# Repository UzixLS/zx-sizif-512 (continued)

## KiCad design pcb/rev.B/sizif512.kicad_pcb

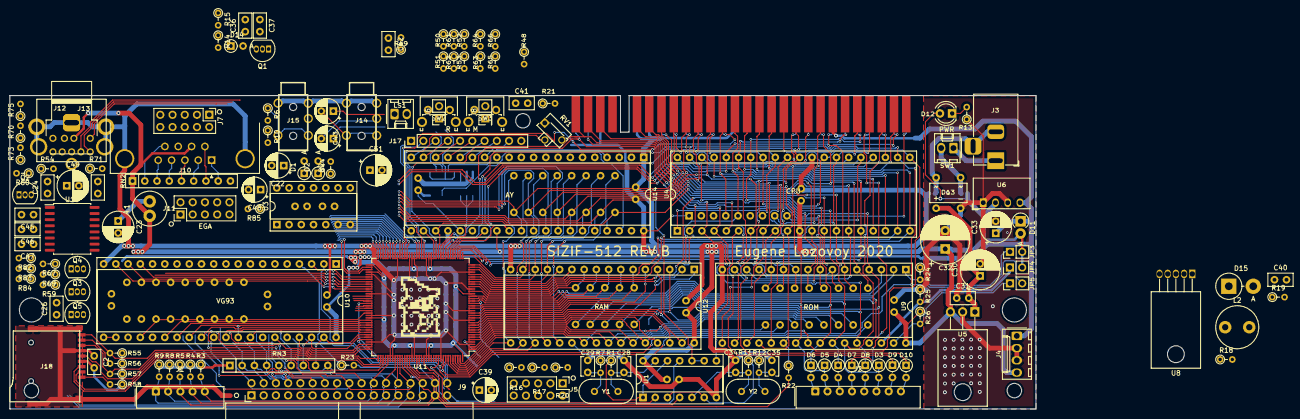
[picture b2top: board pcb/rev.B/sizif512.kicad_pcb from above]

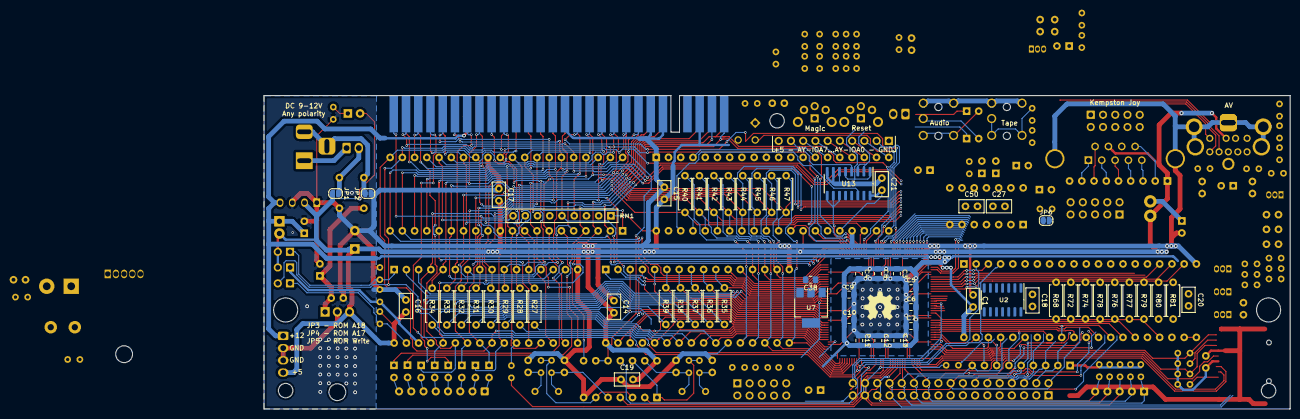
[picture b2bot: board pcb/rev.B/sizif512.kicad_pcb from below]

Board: 2 copper layers, 213.0 x 65.1 mm, 214 parts (61 on the bottom side), 231 nets.

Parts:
C1, C2, C14, C15, C16, C17, C18, C19, C20, C21, C24, C25, C26, C27, C31, C36, C40, C41, C45, C46, C47, C50: 100n; C_Disc_D5.0mm_W2.5mm_P2.50mm
C3, C4, C5, C6, C7, C8, C9, C10, C11, C12, C13, C38: 100n; C_0805_2012Metric_Pad1.15x1.40mm_HandSolder
C22, C43, C44, C48: 10u/16V; CP_Radial_D5.0mm_P2.50mm
C23, C49, C51: 220u/16V; CP_Radial_D6.3mm_P2.50mm
C28, C34: 33p; C_Disc_D3.8mm_W2.6mm_P2.50mm
C29, C35: 47p; C_Disc_D3.8mm_W2.6mm_P2.50mm
C30: 100u/50V; CP_Radial_D8.0mm_P2.50mm
C32: 470u/25V; CP_Radial_D10.0mm_P3.80mm
C33: 100u/25V; CP_Radial_D6.3mm_P2.50mm
C37: 10n; C_Disc_D5.0mm_W2.5mm_P2.50mm
C39: 100u/16V; CP_Radial_D5.0mm_P2.50mm
C42: 47n; C_Disc_D5.0mm_W2.5mm_P2.50mm
D1, D2: 1N4148; D_DO-35_SOD27_P2.54mm_Vertical_AnodeUp
D3, D4, D5, D6, D7, D8, D9, D10, D14: BAT85; D_DO-35_SOD27_P2.54mm_Vertical_AnodeUp
D11: 1N5817; D_DO-41_SOD81_P2.54mm_Vertical_AnodeUp
D12: LED; LED_D4.0mm
D13: DB207; DB-1
D15: D; D_DO-201AD_P5.08mm_Vertical_AnodeUp
H1, H2: MountingHole; MountingHole_5mm
H3, H4, H5: MountingHole; MountingHole_3mm
J1: Conn_01x05; FFC_FPC_1x05
J2: Conn_01x08; FFC_FPC_1x08
J3: DS-210; BarrelJack_Horizontal
J4: WF-4; Molex_KK-254_AE-6410-04A_1x04_P2.54mm_Vertical
J5: JTAG; PinHeader_2x05_P2.54mm_Vertical
J6, J8: Conn_01x02; PinHeader_2x01_P2.54mm_Vertical
J7: Conn_02x05_Top_Bottom; PinHeader_2x05_P2.54mm_Vertical
J9: Conn_02x17_Odd_Even; IDC-Header_2x17_P2.54mm_Horizontal_Mirrored
J10: DB9-M; DSUB-9_Male_Horizontal_P2.77x2.84mm_EdgePinOffset4.94mm_Hou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
J11: Conn_02x05_Odd_Even; PinHeader_2x05_P2.54mm_Vertical
J12: Mini-DIN-9; minidin-9
J13: RCJ-014; CUI_RCJ-01X-WIDE
J14, J15: PJ-313
J16: Conn_02x28_Row_Letter_First; ZX_EDGE
J17: Conn_01x10; PinHeader_1x10_P2.54mm_Vertical
J18: MEM2055-00-190-01-A; GCT-MEM2055-00-190-01-A
JP1, JP2, JP6: SolderJumper_2_Open; SolderJumper-2_P1.3mm_Open_RoundedPad1.0x1.5mm
JP3, JP4, JP5: Jumper; PinHeader_1x02_P2.54mm_Vertical
L1: 220u/0.2A; L_Radial_D7.0mm_P3.00mm
L2: L; L_Radial_D8.7mm_P5.00mm_Fastron_07HCP
LOGO1: Logo_Open_Hardware_Small; OSHW-Symbol_6.7x6mm_SilkScreen
LOGO2: graphic; black-mage2
LS1: WF-2; Molex_KK-254_AE-6410-02A_1x02_P2.54mm_Vertical
Q1: BC547B; TO-92_Inline
Q2, Q3, Q4, Q5: BC547C; TO-92_Inline
R1, R11: 1M; R_Axial_DIN0204_L3.6mm_D1.6mm_P2.54mm_Vertical
R2, R10: 47k; R_Axial_DIN0204_L3.6mm_D1.6mm_P2.54mm_Vertical
R3, R4, R5, R8, R9, R16, R17, R20, R23, R24, R25, R26, R55, R56, R57, R58, R65, R66: 10k; R_Axial_DIN0204_L3.6mm_D1.6mm_P2.54mm_Vertical
R6, R7, R12, R15, R52, R53, R63, R64: 1k; R_Axial_DIN0204_L3.6mm_D1.6mm_P2.54mm_Vertical
R13, R18, R19, R22, R48: 470; R_Axial_DIN0204_L3.6mm_D1.6mm_P2.54mm_Vertical
R14: 220k; R_Axial_DIN0204_L3.6mm_D1.6mm_P2.54mm_Vertical
R21, R85: 100k; R_Axial_DIN0204_L3.6mm_D1.6mm_P2.54mm_Vertical
R27, R28, R29, R30, R31, R32, R33, R34, R35, R36, R37, R38, R39, R40, R41, R42, R43, R44, R45, R46, R47: 1k; R_Axial_DIN0207_L6.3mm_D2.5mm_P7.62mm_Horizontal
R49, R54, R60: 270; R_Axial_DIN0204_L3.6mm_D1.6mm_P2.54mm_Vertical
R50, R51, R61, R62: 2k; R_Axial_DIN0204_L3.6mm_D1.6mm_P2.54mm_Vertical
R59, R67, R69, R70, R73, R75: 68; R_Axial_DIN0204_L3.6mm_D1.6mm_P2.54mm_Vertical
R68, R72, R74, R76, R77, R78, R79, R80, R81: 3.6k; R_Axial_DIN0207_L6.3mm_D2.5mm_P7.62mm_Horizontal
R71, R82, R83, R84: 75; R_Axial_DIN0204_L3.6mm_D1.6mm_P2.54mm_Vertical
RN1, RN2: 10k; R_Array_SIP9
RN3: 4.7k; R_Array_SIP9
RV1: 47k; Potentiometer_Runtron_RM-063_Horizontal
SW1: Conn_01x02; Molex_KK-254_AE-6410-02A_1x02_P2.54mm_Vertical
SW2, SW3: WF-2; SW_Tactile_SPST_Angled_PTS645Vx83-2LFS
U1, U3: 74HCU04; DIP-14_W7.62mm_Socket
U2: 74HCT05; SOIC-14_3.9x8.7mm_P1.27mm
U4: Z84C0008PEC; DIP-40_W15.24mm_Socket
U5: L4940V5 / K7805-2000R3L; TO-220-3_Horizontal_TabDown
U6: AM1S-0512SZ; Converter_DCDC_muRata_CRE1xxxxxx3C_THT
U7: AMS1117-3.3; SOT-223-3_TabPin2
U8: LM2596T-ADJ; TO-220-5_Horizontal_TabDown
U9: 29C040; DIP-32_W15.24mm_Socket
U10: 1818VG93; DIP-40_W15.24mm_Socket
U11: EPM3256ATC144; TQFP-144_20x20mm_P0.5mm
U12: AS6C4008-55PCN; DIP-32_W15.24mm_Socket
U13: 74HCT4053D; SOIC-16_3.9x9.9mm_P1.27mm
U14: AY-3-8310; DIP-40_W15.24mm_Socket
U15: AD724; SOIC-16W_7.5x10.3mm_P1.27mm
Y1: 17.734475 MHz; Crystal_HC49-U_Vertical
Y2: 8 MHz; Crystal_HC49-U_Vertical

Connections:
+3V3: C2.2, C3.2, C4.2, C5.2, C6.2, C7.2, C8.2, C9.2, C10.2, C11.2, C12.2, C13.2, C39.1, J5.4, J18.4, R16.2, R17.2, R55.1, R56.1, R57.1, R58.1, U7.2, U11.24, U11.50, U11.51, U11.58, U11.73, U11.76, U11.95, U11.115, U11.123, U11.130, U11.144
+5V: C14.2, C15.2, C16.2, C17.2, C18.2, C19.2, C20.2, C21.2, C32.1, C38.2, D11.2, D12.2, J4.4, J7.4, J10.7, J12.2, J16.A3, J17.10, JP1.2, JP3.2, JP4.2, JP6.1, L1.1, R3.1, R4.1, R5.1, R8.1, R9.1, R14.1, R21.2, R23.1, R26.1, RN1.1, RN2.1, RN3.1, U1.14, U2.14, U4.11, U5.3, U6.2, U7.3, U9.32, U10.21, U10.22, U12.32, U13.16, U14.25, U14.28, U14.40
+5VA: C23.1, C24.2, C25.2, C26.2, C27.2, L1.2, Q2.1, Q3.1, Q4.1, Q5.1, U3.14, U15.4, U15.5, U15.14, U15.15
+12V: C1.2, C33.1, D11.1, J4.1, J16.B22, U6.4, U10.40
/<: J16.A13, R48.1, U11.54
/>: R48.2, U11.53
/A0: J16.A9, R27.1, U4.30, U9.12
/A1: J16.A10, R28.1, U4.31, U9.11
/A2: J16.A11, R29.1, U4.32, U9.10
/A3: J16.A12, R30.1, U4.33, U9.9
/A4: J16.A24, R31.1, U4.34, U9.8
/A5: J16.A23, R32.1, U4.35, U9.7, U10.5
/A6: J16.A22, R33.1, U4.36, U9.6, U10.6
/A7: J16.A21, R34.1, U4.37, U9.5
/A8: D3.1, J16.B26, R35.1, U4.38, U9.27
/A9: D4.1, J16.A27, R36.1, U4.39, U9.26
/A10: D5.1, J16.B27, R37.1, U4.40, U9.23
/A11: D6.1, J16.A28, R38.1, U4.1, U9.25
/A12: D7.1, J16.A2, R39.1, U4.2, U9.4
/A13: D8.1, J16.B2, U4.3, U9.28, U11.132
/A14: D9.1, J16.A1, U4.4, U11.46
/A15: D10.1, J16.B1, U4.5, U11.48
/AY_ABC: U11.43, U13.9, U13.10, U13.11
/AY_BC1: U11.41, U14.29
/AY_BDIR: U11.42, U14.27
/AY_CLK: U11.49, U14.22
/Blue: J11.1, R74.1, U11.74
/Bright: J11.4, J11.8, J11.9, R76.2, R77.2, R78.2, U11.70
/CLK8: U1.4, U11.125
/CLK17: U1.2, U11.128, U15.3
/CLKCPU: U1.8, U4.6
/CLKCPU0: U1.11, U11.134
/Csync: Q2.2, U11.75, U15.16
/D0: J16.B6, R40.1, U4.14, U9.13, U10.7, U14.37
/D1: J16.B7, R41.1, U4.15, U9.14, U10.8, U14.36
/D2: J16.B8, R42.1, U4.12, U9.15, U10.9, U14.35
/D3: J16.B11, R43.1, U4.8, U9.17, U10.10, U14.34
/D4: J16.B12, R44.1, U4.7, U9.18, U10.11, U14.33
/D5: J16.B10, R45.1, U4.9, U9.19, U10.12, U14.32
/D6: J16.B9, R46.1, U4.10, U9.20, U10.13, U14.31
/D7: J16.B3, R47.1, U4.13, U9.21, U10.14, U14.30
/FD_CLK: U10.24, U11.93
/FD_CS: U10.3, U11.78
/FD_DDEN: U10.37, U11.106
/FD_DIR: U2.3, U10.16
/FD_DISK0: J9.14, U11.92
/FD_DISK1: J9.12, RN3.5, U11.86
/FD_DRQ: RN3.7, U10.38, U11.103
/FD_HLT: U10.23, U11.90
/FD_INDEX: J9.8, RN3.2, U11.91
/FD_INDEX1: U10.35, U11.107
/FD_INTRQ: RN3.8, U10.39, U11.102
/FD_MOTOR: U2.13, U10.28, U10.32, U11.98
/FD_RAWR: U10.27, U11.97
/FD_RDAT: J9.30, RN3.9, U11.84
/FD_RST: U10.19, U11.83
/FD_S: U10.26, U11.96
/FD_SIDE: U2.9, U11.88
/FD_SL: U10.17, U11.81
/FD_SR: U10.18, U11.82
/FD_STEP: U2.1, U10.15
/FD_TR00: J9.26, RN3.3, U10.34
/FD_TR43: U10.29, U11.99
/FD_WD: U10.31, U11.100
/FD_WDAT: U2.5, U11.87
/FD_WF_DE: RN3.6, U10.33, U11.101
/FD_WPT: J9.28, RN3.4, U10.36
/FD_WSTB: U2.11, U10.30
/Green: J11.2, R72.1, U11.71
/Hsync: J11.7, U11.80
/KA8: D3.2, J2.6
/KA9: D4.2, J2.3
/KA10: D5.2, J2.2
/KA11: D6.2, J2.1
/KA12: D7.2, J2.4
/KA13: D8.2, J2.5
/KA14: D9.2, J2.7
/KA15: D10.2, J2.8
/KD0: J1.1, R9.2, U11.116
/KD1: J1.2, R8.2, U11.113
/KD2: J1.3, R5.2, U11.121
/KD3: J1.4, R4.2, U11.120
/KD4: J1.5, R3.2, U11.119
/RA14: U9.29, U11.25
/RA15: U9.3, U11.22
/RA16: U9.2, U11.23
/Red: J11.3, R68.1, U11.72
/SD_CD: J18.9, R55.2, U11.108
/SD_CS: J18.2, U11.111
/SD_MISO: J18.7, R57.2, U11.109
/SD_MOSI: J18.3, U11.112
/SD_SCK: J18.5, U11.110
/SND_DAC: R49.1, U11.61
/SND_L: C43.2, J12.8, J14.T
/SND_MONO: C48.2, J12.6
/SND_R: C44.2, J12.9, J14.R
/TAPE_IN: J15.R, J15.T, R6.1
/TAPE_IN0: RN2.9, U3.12, U11.55
/TCK: J5.1, R20.2, U11.89
/TDI: J5.9, R16.1, U11.4
/TDO: J5.3, U11.104
/TMS: J5.5, R17.1, U11.20
/VA0: R27.2, U11.6, U12.27
/VA1: R28.2, U11.7, U12.28
/VA2: R29.2, U11.5, U12.26
/VA3: R30.2, U11.2, U12.25
/VA4: R31.2, U11.143, U12.23
/VA5: R32.2, U11.12, U12.4
/VA6: R33.2, U11.11, U12.3
/VA7: R34.2, U11.10, U12.31
/VA8: R35.2, U11.27, U12.10
/VA9: R36.2, U11.21, U12.9
/VA10: R37.2, U11.19, U12.8
/VA11: R38.2, U11.18, U12.7
/VA12: R39.2, U11.16, U12.6
/VA13: U11.15, U12.5
/VA14: U11.34, U12.12
/VA15: U11.32, U12.11
/VA16: U11.28, U12.2
/VA17: U11.9, U12.30
/VA18: U11.14, U12.1
/VD0: R40.2, U11.142, U12.21
/VD1: R41.2, U11.35, U12.13
/VD2: R42.2, U11.141, U12.20
/VD3: R43.2, U11.36, U12.14
/VD4: R44.2, U11.138, U12.19
/VD5: R45.2, U11.37, U12.15
/VD6: R46.2, U11.139, U12.18
/VD7: R47.2, U11.140, U12.17
/VID_B: J12.1, R75.2
/VID_COMP: J12.4, J13.1, R71.2
/VID_G: J12.3, R73.2
/VID_R: J12.7, R70.2
/VID_SYNC: J12.5, R54.2
/Vsync: J11.6, U11.79
/~BUSACK: J16.A26, U4.23
/~BUSRQ: J16.A19, RN1.9, U4.25
/~CLKCPU: J16.A8, U1.9, U1.10
/~HALT: J16.B15, U4.18
/~INT: J16.B13, RN1.4, U4.16, U11.38
/~IORQ: J16.B17, U4.20, U11.31
/~JOY_B1: J7.2, J10.6, RN2.7, U11.63
/~JOY_B2: J7.8, J10.9, RN2.2, U11.69
/~JOY_B3: J7.9, J10.5, RN2.3, U11.68
/~JOY_DOWN: J7.3, J10.2, RN2.6, U11.65
/~JOY_LEFT: J7.5, J10.3, RN2.5, U11.66
/~JOY_RIGHT: J7.7, J10.4, RN2.4, U11.67
/~JOY_UP: J7.1, J10.1, RN2.8, U11.62
/~M1: J16.B24, U4.27, U11.40
/~MREQ: J16.B16, U4.19, U11.30
/~NMI: J16.B14, RN1.5, U4.17, U11.39
/~RD: J16.B18, RN1.6, U4.21, U9.24, U10.4, U11.137
/~RFSH: J16.B25, U4.28, U11.29
/~ROMCS: J16.A25, R22.1, U9.22
/~ROMCS0: R22.2, U11.122
/~RSTCPU: J16.A20, RN1.7, U4.26, U11.47, U14.23
/~VRD: U11.1, U12.24
/~VWR: U11.8, U12.29
/~WAIT: J16.B21, RN1.8, U4.24
/~WR: J16.B19, JP5.2, U4.22, U10.2, U11.136
GND: C1.1, C2.1, C3.1, C4.1, C5.1, C6.1, C7.1, C8.1, C9.1, C10.1, C11.1, C12.1, C13.1, C14.1, C15.1, C16.1, C17.1, C18.1, C19.1, C20.1, C21.1, C23.2, C24.1, C25.1, C26.1, C27.1, C28.1, C29.1, C30.2, C31.1, C32.2, C33.2, C34.1, C35.1, C37.1, C38.1, C39.2, C41.1, C42.1, D13.1, D14.2, D15.2, J4.2, J4.3, J5.2, J5.10, J6.2, J7.6, J7.10, J8.2, J9.1, J9.3, J9.5, J9.7, J9.9, J9.11, J9.13, J9.15, J9.17, J9.19, J9.21, J9.23, J9.25, J9.27, J9.29, J9.31, J9.33, J10.0, J10.8, J11.5, J12.0, J13.2, J14.S, J15.S, J16.A6, J16.A7, J16.A14, J17.1, J18.6, J18.10, JP2.2, LS1.2, Q1.3, R10.1, R13.1, R20.1, R24.1, R25.1, R60.2, R63.2, R64.2, R79.2, R80.2, R81.2, R82.2, R83.2, R84.2, RV1.3, SW2.1, SW3.1, U1.7, U2.7, U3.7, U4.29, U5.2, U6.1, U6.3, U7.1, U8.3, U8.5, U9.16, U10.20, U11.3, U11.13, U11.17, U11.26, U11.33, U11.52, U11.57, U11.59, U11.64, U11.77, U11.85, U11.94, U11.105, U11.114, U11.124, U11.129, U11.135, U12.16, U12.22, U13.6, U13.7, U13.8, U14.1, U14.24, U15.1, U15.2, U15.12, U15.13
unnamed: C22.1, D1.2, D2.1, R10.2, U3.9
unnamed: C22.2, R6.2
unnamed: C28.2, R1.2, U1.13, Y1.1
unnamed: C29.2, R7.2, Y1.2
unnamed: C30.1, C31.2, D13.4, U5.1
unnamed: C34.2, R11.2, U1.5, Y2.1
unnamed: C35.2, R12.2, Y2.2
unnamed: C36.1, C37.2, D14.1, Q1.2, R14.2
unnamed: C36.2, R15.2
unnamed: C42.2, R49.2, R50.2, R51.1
unnamed: C43.1, R51.2, R52.1, R62.1, R64.1, R66.1
unnamed: C44.1, R50.1, R53.2, R61.2, R63.1, R65.2
unnamed: C45.1, R59.2
unnamed: C45.2, U15.6
unnamed: C46.1, R67.2
unnamed: C46.2, U15.7
unnamed: C47.1, R69.2
unnamed: C47.2, U15.8
unnamed: C48.1, R65.1, R66.2, RV1.2
unnamed: C49.1, U15.10
unnamed: C49.2, R71.1
unnamed: C50.1, R85.1, U3.1
unnamed: C50.2, RV1.1
unnamed: C51.1, R85.2, U3.6
unnamed: C51.2, LS1.1
unnamed: D1.1, D2.2, R2.1, U3.8, U3.11
unnamed: D12.1, R13.2
unnamed: D13.2, JP1.1, SW1.2
unnamed: D13.3, J3.2, J3.3, JP2.1
unnamed: J3.1, SW1.1
unnamed: J9.10, J9.16, U2.12
unnamed: J9.18, U2.4
unnamed: J9.20, U2.2
unnamed: J9.22, U2.6
unnamed: J9.24, U2.10
unnamed: J9.32, U2.8
unnamed: J11.10, JP6.2
unnamed: J17.2, U14.21
unnamed: J17.3, U14.20
unnamed: J17.4, U14.19
unnamed: J17.5, U14.18
unnamed: J17.6, U14.17
unnamed: J17.7, U14.16
unnamed: J17.8, U14.15
unnamed: J17.9, U14.14
unnamed: J18.1, R58.2
unnamed: J18.8, R56.2
unnamed: JP3.1, R24.2, U9.1
unnamed: JP4.1, R25.2, U9.30
unnamed: JP5.1, R26.2, U9.31
unnamed: Q2.3, R54.1, R60.1
unnamed: Q3.2, R68.2, R78.1, R81.1
unnamed: Q3.3, R59.1, R70.1, R82.1
unnamed: Q4.2, R72.2, R77.1, R80.1
unnamed: Q4.3, R67.1, R73.1, R83.1
unnamed: Q5.2, R74.2, R76.1, R79.1
unnamed: Q5.3, R69.1, R75.1, R84.1
unnamed: R1.1, R7.1, U1.1, U1.12
unnamed: R2.2, U3.10, U3.13
unnamed: R11.1, R12.1, U1.3, U1.6
unnamed: R52.2, U13.12, U13.13
unnamed: R53.1, U13.2, U13.3
unnamed: R61.1, R62.2, U13.1, U13.5
unnamed: U3.2, U3.3
unnamed: U3.4, U3.5
unnamed: U13.4, U14.3
unnamed: U13.14, U14.4
unnamed: U13.15, U14.38
~MAGIC: J8.1, R23.2, SW3.2, U11.126
~RST: C41.2, J6.1, R21.1, SW2.2, U11.127
